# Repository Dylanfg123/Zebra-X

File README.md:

# ZeBra-X: A Xilinx Zynq Demo Board

The ZeBra-X board is my take on the Phil's Lab ZettBrett board. The heart of this board is a Xilinx Zynq (XC7Z010-2CLG400) SOC demo board featuring a 1Gig ethernet interface, USB-UART/USB-JTAG FTDI, USB HS, 1GB DDR3 memory, 4GB eMMC memory, and 16MB QSPI Flash. The main purpose of this board is to learn more about advanced PCB design techniques and get more familiar with the Xilinx software suite.

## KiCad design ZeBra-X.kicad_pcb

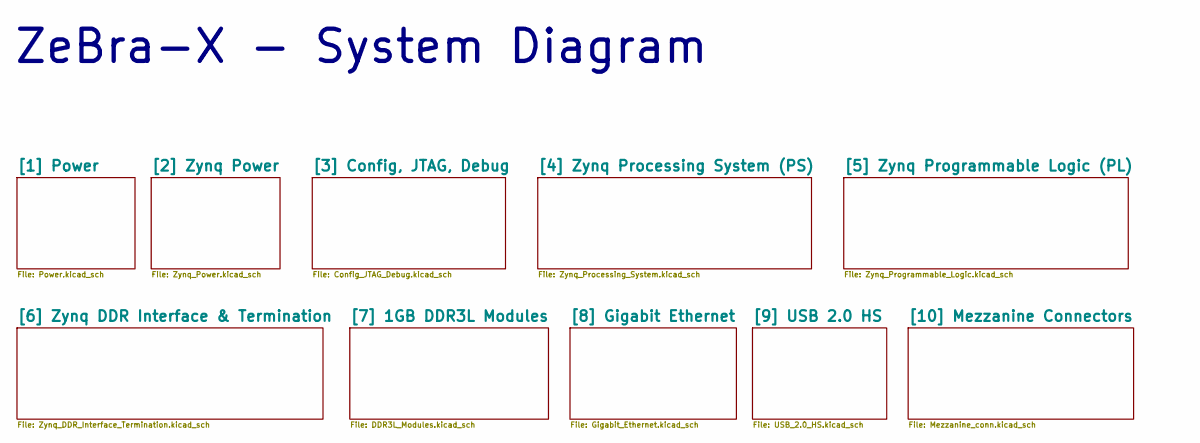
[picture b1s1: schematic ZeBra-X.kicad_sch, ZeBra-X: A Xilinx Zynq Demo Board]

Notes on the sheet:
ZeBra-X - System Diagram

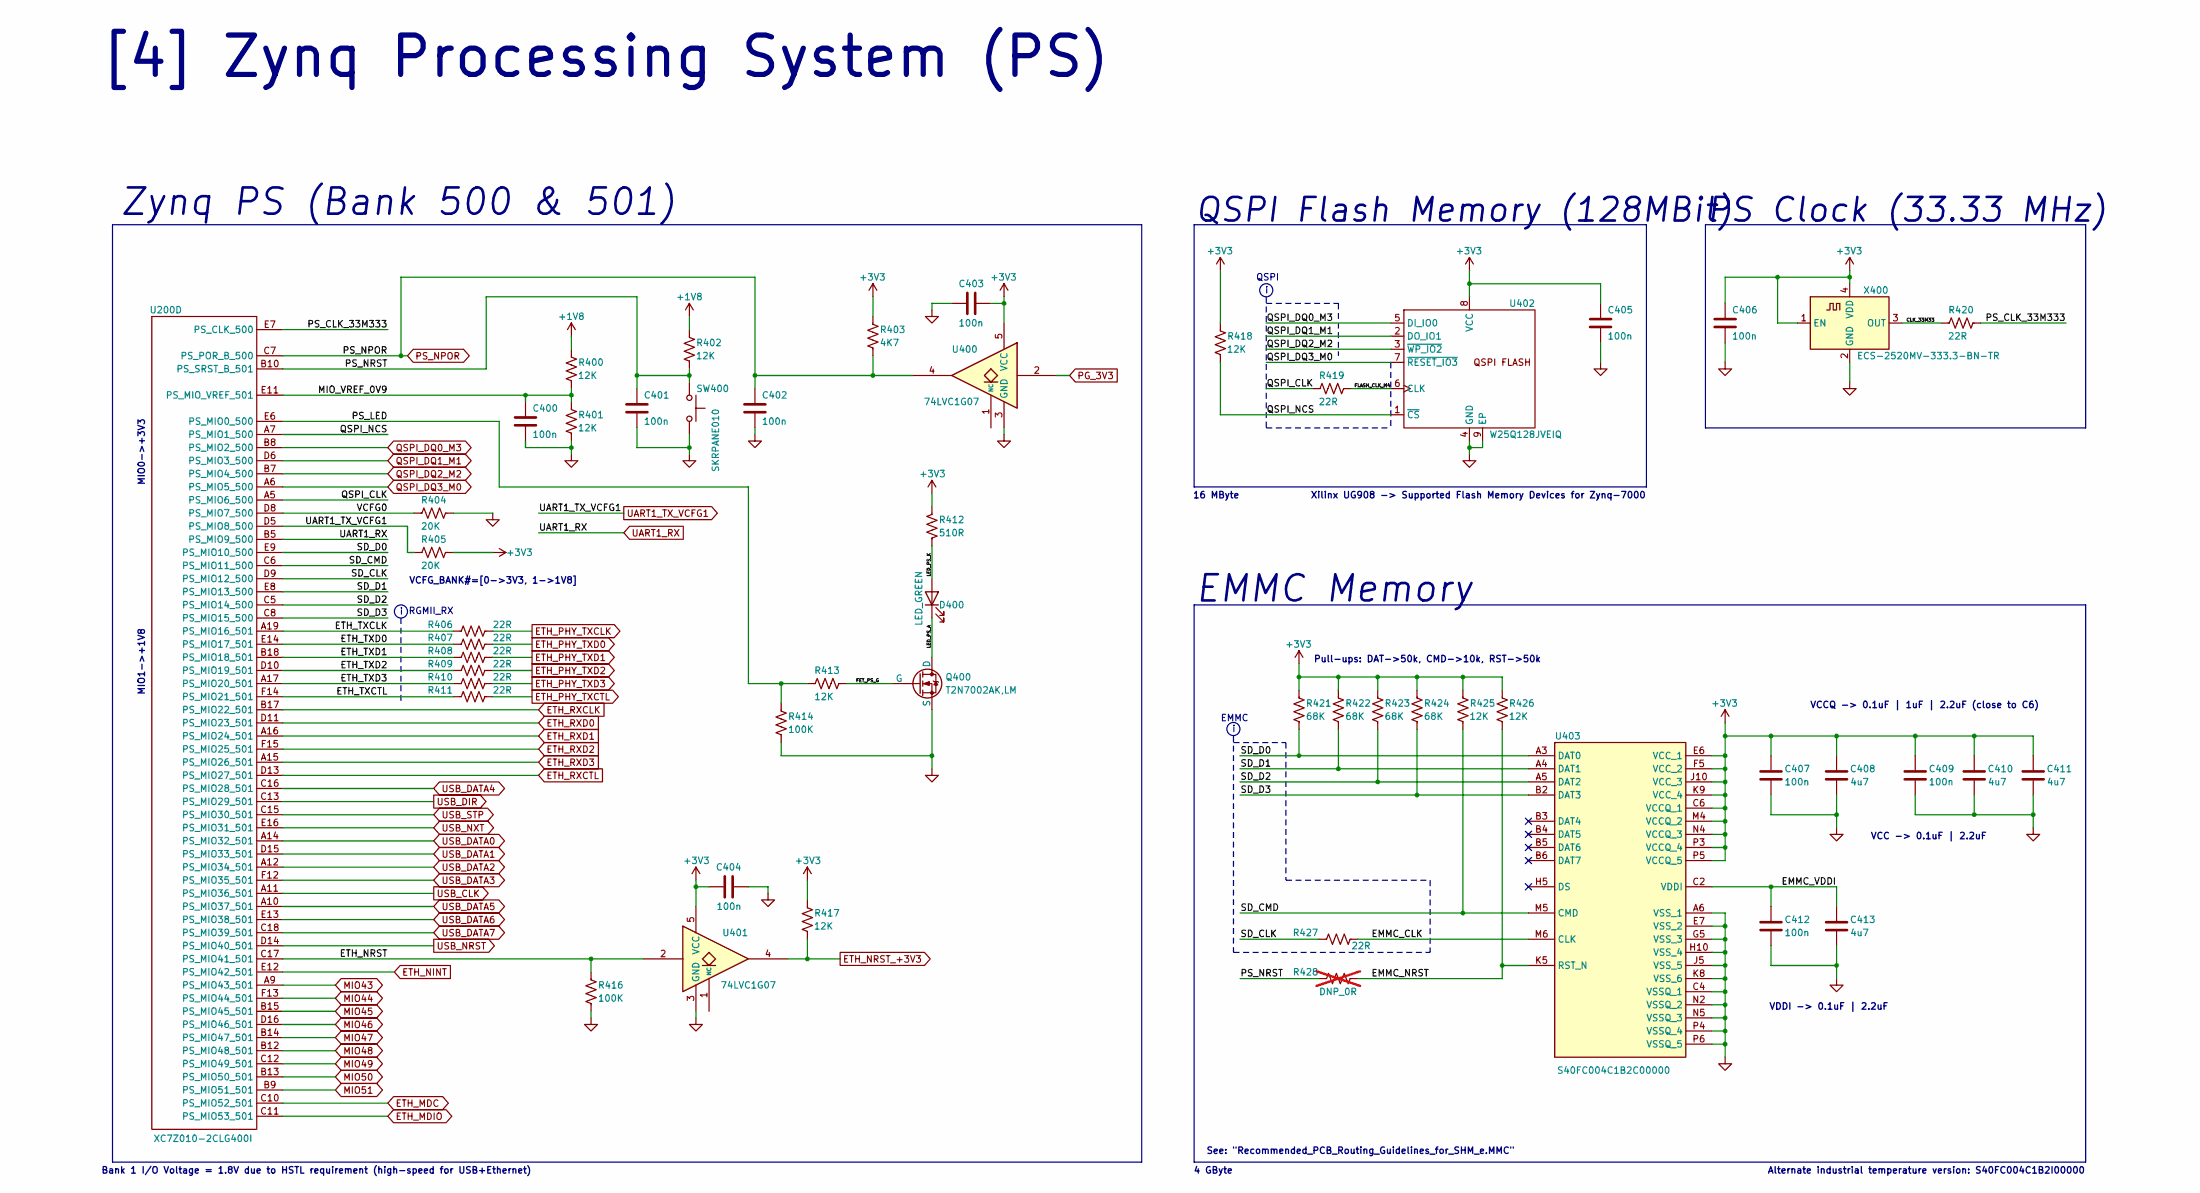
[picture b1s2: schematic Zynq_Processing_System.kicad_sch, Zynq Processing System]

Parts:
C400, C401, C402, C403, C404, C405, C406, C407, C409, C412: 100n; C_0402_1005Metric; Manufacturer PN CC0402KRX5R8BB104; LCSC PN C106256
C408, C410, C411, C413: 4u7; C_0402_1005Metric; Manufacturer PN CL05A475MP5NRNC; LCSC PN C23733
D400: LED_GREEN; LED_0402_1005Metric; Manufacturer PN SZYY0402YG; LCSC PN C434449
Q400: T2N7002AK,LM; SOT23_TOS; Manufacturer PN T2N7002AK,LM; LCSC PN C516175
R400, R401, R402, R413, R417, R418, R425, R426: 12K; R_0402_1005Metric; Manufacturer PN RTT021202FTH; LCSC PN C102781
R403: 4K7; R_0402_1005Metric; Manufacturer PN RC0402FR-074K7L; LCSC PN C105871
R404, R405: 20K; R_0402_1005Metric; Manufacturer PN RC0402FR-0720KL; LCSC PN C93942
R406, R407, R408, R409, R410, R411, R419, R420, R427: 22R; R_0402_1005Metric; Manufacturer PN RC0402FR-0722RL; LCSC PN C114765
R412: 510R; R_0402_1005Metric; Manufacturer PN RC0402FR-07510RL; LCSC PN C276273
R414, R416: 100K; R_0402_1005Metric; Manufacturer PN RC0402FR-07100KL; LCSC PN C60491
R421, R422, R423, R424: 68K; R_0402_1005Metric; Manufacturer PN RC0402FR-0768KL; LCSC PN C137947
R428: DNP_0R; R_0402_1005Metric; not fitted
SW400: SKRPANE010; SW_Push_1P1T_NO_Vertical_Wuerth_434133025816; Manufacturer PN SKRPANE010; LCSC PN C470426
U200: XC7Z010-2CLG400I; CLG400_XIL; Manufacturer PN XC7Z010-2CLG400I; LCSC PN C2840993
U400, U401: 74LVC1G07; SOT-23-5; Manufacturer PN SN74LVC1G07DBVT; LCSC PN C2867373
U402: W25Q128JVEIQ; WSON-8-1EP_8x6mm_P1.27mm_EP3.4x4.3mm; Manufacturer PN W25Q128JVEIQ
U403: S40FC004C1B2C00000; BGA153C50P14X14_900X750X80; Manufacturer PN S40FC004C1B2C00000
X400: ECS-2520MV-333.3-BN-TR; Oscillator_SMD_ECS_2520MV-xxx-xx-4Pin_2.5x2.0mm; Manufacturer PN ECS-2520MV-333.3-BN-TR

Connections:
+1V8: R400.2, R402.2; also elsewhere on the board
+3V3: C403.1, C404.1, C405.1, C406.1, C407.1, C408.2, C409.1, C410.2, C411.2, R403.1, R405.1, R412.2, R417.2, R418.2, R421.1, R422.1, R423.1, R424.1, R425.2, R426.2, U400.5 (VCC), U401.5 (VCC), U402.8 (VCC), U403.C6 (VCCQ_1), U403.E6 (VCC_1), U403.F5 (VCC_2), U403.J10 (VCC_3), U403.K9 (VCC_4), U403.M4 (VCCQ_2), U403.N4 (VCCQ_3), U403.P3 (VCCQ_4), U403.P5 (VCCQ_5), X400.1 (EN), X400.4 (VDD); also elsewhere on the board
/[4] Zynq Processing System (PS)/CLK_33M33: R420.1, X400.3 (OUT)
/[4] Zynq Processing System (PS)/EMMC_CLK: R427.2, U403.M6 (CLK)
/[4] Zynq Processing System (PS)/EMMC_NRST: R426.1, R428.1, U403.K5 (RST_N)
/[4] Zynq Processing System (PS)/EMMC_VDDI: C412.1, C413.2, U403.C2 (VDDI)
/[4] Zynq Processing System (PS)/ETH_NRST: R416.1, U200.C17 (PS_MIO41_501), U401.2
/[4] Zynq Processing System (PS)/ETH_TXCLK: R406.1, U200.A19 (PS_MIO16_501)
/[4] Zynq Processing System (PS)/ETH_TXCTL: R411.1, U200.F14 (PS_MIO21_501)
/[4] Zynq Processing System (PS)/ETH_TXD0: R407.1, U200.E14 (PS_MIO17_501)
/[4] Zynq Processing System (PS)/ETH_TXD1: R408.1, U200.B18 (PS_MIO18_501)
/[4] Zynq Processing System (PS)/ETH_TXD2: R409.1, U200.D10 (PS_MIO19_501)
/[4] Zynq Processing System (PS)/ETH_TXD3: R410.1, U200.A17 (PS_MIO20_501)
/[4] Zynq Processing System (PS)/FET_PS_G: Q400.1 (G), R413.1
/[4] Zynq Processing System (PS)/FLASH_CLK_M4: R419.2, U402.6 (CLK)
/[4] Zynq Processing System (PS)/LED_PS_A: D400.1 (K), Q400.3 (D)
/[4] Zynq Processing System (PS)/LED_PS_K: D400.2 (A), R412.1
/[4] Zynq Processing System (PS)/MIO_VREF_0V9: C400.1, R400.1, R401.2, U200.E11 (PS_MIO_VREF_501)
/[4] Zynq Processing System (PS)/PS_CLK_33M333: R420.2, U200.E7 (PS_CLK_500)
/[4] Zynq Processing System (PS)/PS_LED: R413.2, R414.1, U200.E6 (PS_MIO0_500)
/[4] Zynq Processing System (PS)/PS_NRST: C401.1, R402.1, R428.2, SW400.1, U200.B10 (PS_SRST_B_501)
/[4] Zynq Processing System (PS)/QSPI_CLK: R419.1, U200.A5 (PS_MIO6_500)
/[4] Zynq Processing System (PS)/QSPI_NCS: R418.1, U200.A7 (PS_MIO1_500), U402.1 (~CS)
/[4] Zynq Processing System (PS)/SD_CLK: R427.1, U200.D9 (PS_MIO12_500)
/[4] Zynq Processing System (PS)/SD_CMD: R425.1, U200.C6 (PS_MIO11_500), U403.M5 (CMD)
/[4] Zynq Processing System (PS)/SD_D0: R421.2, U200.E9 (PS_MIO10_500), U403.A3 (DAT0)
/[4] Zynq Processing System (PS)/SD_D1: R422.2, U200.E8 (PS_MIO13_500), U403.A4 (DAT1)
/[4] Zynq Processing System (PS)/SD_D2: R423.2, U200.C5 (PS_MIO14_500), U403.A5 (DAT2)
/[4] Zynq Processing System (PS)/SD_D3: R424.2, U200.C8 (PS_MIO15_500), U403.B2 (DAT3)
/[4] Zynq Processing System (PS)/VCFG0: R404.2, U200.D8 (PS_MIO7_500)
ETH_MDC: U200.C10 (PS_MIO52_501); also elsewhere on the board
ETH_MDIO: U200.C11 (PS_MIO53_501); also elsewhere on the board
ETH_NINT: U200.E12 (PS_MIO42_501); also elsewhere on the board
ETH_NRST_+3V3: R417.1, U401.4; also elsewhere on the board
ETH_PHY_TXCLK: R406.2; also elsewhere on the board
ETH_PHY_TXCTL: R411.2; also elsewhere on the board
ETH_PHY_TXD0: R407.2; also elsewhere on the board
ETH_PHY_TXD1: R408.2; also elsewhere on the board
ETH_PHY_TXD2: R409.2; also elsewhere on the board
ETH_PHY_TXD3: R410.2; also elsewhere on the board
ETH_RXCLK: U200.B17 (PS_MIO22_501); also elsewhere on the board
ETH_RXCTL: U200.D13 (PS_MIO27_501); also elsewhere on the board
ETH_RXD0: U200.D11 (PS_MIO23_501); also elsewhere on the board
ETH_RXD1: U200.A16 (PS_MIO24_501); also elsewhere on the board
ETH_RXD2: U200.F15 (PS_MIO25_501); also elsewhere on the board
ETH_RXD3: U200.A15 (PS_MIO26_501); also elsewhere on the board
GND: C400.2, C401.2, C402.2, C403.2, C404.2, C405.2, C406.2, C407.2, C408.1, C409.2, C410.1, C411.1, C412.2, C413.1, Q400.2 (S), R401.1, R404.1, R414.2, R416.2, SW400.2, U400.3 (GND), U401.3 (GND), U402.4 (GND), U402.9 (EP), U403.A6 (VSS_1), U403.C4 (VSSQ_1), U403.E7 (VSS_2), U403.G5 (VSS_3), U403.H10 (VSS_4), U403.J5 (VSS_5), U403.K8 (VSS_6), U403.N2 (VSSQ_2), U403.N5 (VSSQ_3), U403.P4 (VSSQ_4), U403.P6 (VSSQ_5), X400.2 (GND); also elsewhere on the board
MIO43: U200.A9 (PS_MIO43_501)
MIO44: U200.F13 (PS_MIO44_501)
MIO45: U200.B15 (PS_MIO45_501)
MIO46: U200.D16 (PS_MIO46_501)
MIO47: U200.B14 (PS_MIO47_501)
MIO48: U200.B12 (PS_MIO48_501)
MIO49: U200.C12 (PS_MIO49_501); also elsewhere on the board
MIO50: U200.B13 (PS_MIO50_501); also elsewhere on the board
MIO51: U200.B9 (PS_MIO51_501); also elsewhere on the board
PG_3V3: U400.2; also elsewhere on the board
PS_NPOR: C402.1, R403.2, U200.C7 (PS_POR_B_500), U400.4; also elsewhere on the board
QSPI_DQ0_M3: U200.B8 (PS_MIO2_500), U402.5 (DI_IO0); also elsewhere on the board
QSPI_DQ1_M1: U200.D6 (PS_MIO3_500), U402.2 (DO_IO1); also elsewhere on the board
QSPI_DQ2_M2: U200.B7 (PS_MIO4_500), U402.3 (~WP_IO2); also elsewhere on the board
QSPI_DQ3_M0: U200.A6 (PS_MIO5_500), U402.7 (~RESET_IO3); also elsewhere on the board
UART1_RX: U200.B5 (PS_MIO9_500); also elsewhere on the board
UART1_TX_VCFG1: R405.2, U200.D5 (PS_MIO8_500); also elsewhere on the board
USB_CLK: U200.A11 (PS_MIO36_501); also elsewhere on the board
USB_DATA0: U200.A14 (PS_MIO32_501); also elsewhere on the board
USB_DATA1: U200.D15 (PS_MIO33_501); also elsewhere on the board
USB_DATA2: U200.A12 (PS_MIO34_501); also elsewhere on the board
USB_DATA3: U200.F12 (PS_MIO35_501); also elsewhere on the board
USB_DATA4: U200.C16 (PS_MIO28_501); also elsewhere on the board
USB_DATA5: U200.A10 (PS_MIO37_501); also elsewhere on the board
USB_DATA6: U200.E13 (PS_MIO38_501); also elsewhere on the board
USB_DATA7: U200.C18 (PS_MIO39_501); also elsewhere on the board
USB_DIR: U200.C13 (PS_MIO29_501); also elsewhere on the board
USB_NRST: U200.D14 (PS_MIO40_501); also elsewhere on the board
USB_NXT: U200.E16 (PS_MIO31_501); also elsewhere on the board
USB_STP: U200.C15 (PS_MIO30_501); also elsewhere on the board

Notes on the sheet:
VCFG_BANK#=[0->3V3, 1->1V8]
16 MByte
See: "Recommended_PCB_Routing_Guidelines_for_SHM_e.MMC"
EMMC Memory
MIO1->+1V8
Xilinx UG908 -> Supported Flash Memory Devices for Zynq-7000
VDDI -> 0.1uF | 2.2uF
VCC -> 0.1uF | 2.2uF
Zynq PS (Bank 500 & 501)
RGMII_RX
QSPI
Alternate industrial temperature version: S40FC004C1B2I00000
Pull-ups: DAT->50k, CMD->10k, RST->50k
VCCQ -> 0.1uF | 1uF | 2.2uF (close to C6)
Bank 1 I/O Voltage = 1.8V due to HSTL requirement (high-speed for USB+Ethernet)
EMMC
4 GByte
QSPI Flash Memory (128MBit)
[4] Zynq Processing System (PS)
PS Clock (33.33 MHz)
MIO0->+3V3

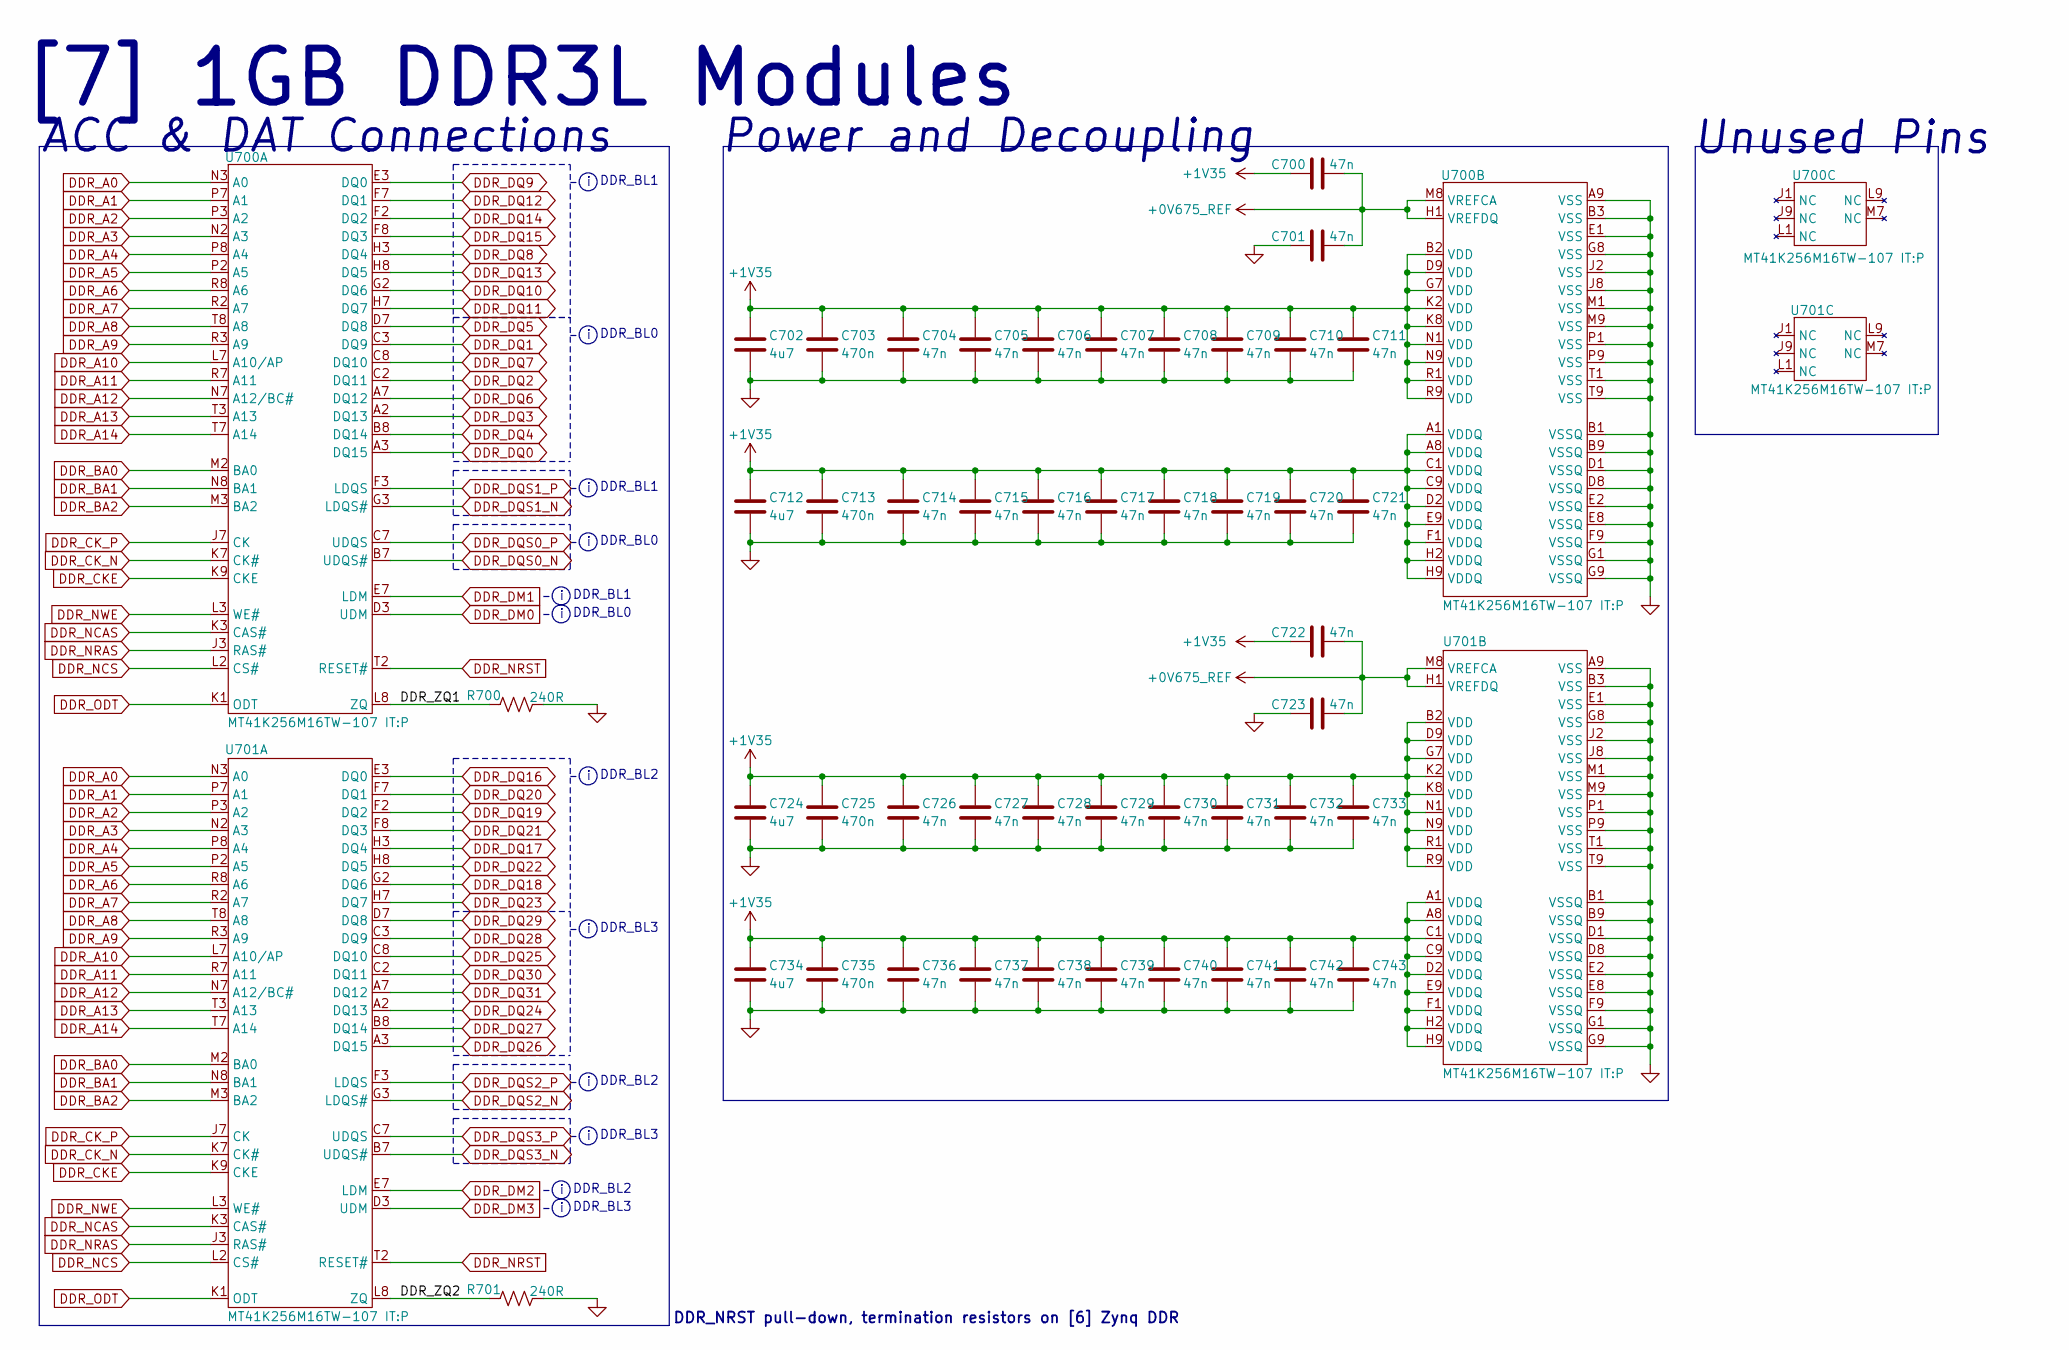
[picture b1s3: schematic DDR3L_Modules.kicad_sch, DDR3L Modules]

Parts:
C700, C701, C704, C705, C706, C707, C708, C709, C710, C711, C714, C715, C716, C717, C718, C719, C720, C721, C722, C723, C726, C727, C728, C729, C730, C731, C732, C733, C736, C737, C738, C739, C740, C741, C742, C743: 47n; C_0201_0603Metric; Manufacturer PN GRT033R60J473KE01D; LCSC PN C126621
C702, C712, C724, C734: 4u7; C_0402_1005Metric; Manufacturer PN CL05A475MP5NRNC; LCSC PN C23733
C703, C713, C725, C735: 470n; C_0201_0603Metric; Manufacturer PN GRM033R60J474KE90D; LCSC PN C85926
R700, R701: 240R; R_0402_1005Metric; Manufacturer PN RC0402FR-07240RL; LCSC PN C114755
U700, U701: MT41K256M16TW-107 IT:P; FBGA96_TW_MRN; Manufacturer PN MT41K256M16TW-107 IT:P; LCSC PN C367428

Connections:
+0V675_REF: C700.2, C701.2, C722.2, C723.2, U700.H1 (VREFDQ), U700.M8 (VREFCA), U701.H1 (VREFDQ), U701.M8 (VREFCA); also elsewhere on the board
+1V35: C700.1, C702.1, C703.1, C704.1, C705.1, C706.1, C707.1, C708.1, C709.1, C710.1, C711.1, C712.1, C713.1, C714.1, C715.1, C716.1, C717.1, C718.1, C719.1, C720.1, C721.1, C722.1, C724.1, C725.1, C726.1, C727.1, C728.1, C729.1, C730.1, C731.1, C732.1, C733.1, C734.1, C735.1, C736.1, C737.1, C738.1, C739.1, C740.1, C741.1, C742.1, C743.1, U700.A1 (VDDQ), U700.A8 (VDDQ), U700.B2 (VDD), U700.C1 (VDDQ), U700.C9 (VDDQ), U700.D2 (VDDQ), U700.D9 (VDD), U700.E9 (VDDQ), U700.F1 (VDDQ), U700.G7 (VDD), U700.H2 (VDDQ), U700.H9 (VDDQ), U700.K2 (VDD), U700.K8 (VDD), U700.N1 (VDD), U700.N9 (VDD), U700.R1 (VDD), U700.R9 (VDD), U701.A1 (VDDQ), U701.A8 (VDDQ), U701.B2 (VDD), U701.C1 (VDDQ), U701.C9 (VDDQ), U701.D2 (VDDQ), U701.D9 (VDD), U701.E9 (VDDQ), U701.F1 (VDDQ), U701.G7 (VDD), U701.H2 (VDDQ), U701.H9 (VDDQ), U701.K2 (VDD), U701.K8 (VDD), U701.N1 (VDD), U701.N9 (VDD), U701.R1 (VDD), U701.R9 (VDD); also elsewhere on the board
/[7] 1GB DDR3L Modules/DDR_ZQ1: R700.1, U700.L8 (ZQ)
/[7] 1GB DDR3L Modules/DDR_ZQ2: R701.1, U701.L8 (ZQ)
DDR_A0: U700.N3 (A0), U701.N3 (A0); also elsewhere on the board
DDR_A1: U700.P7 (A1), U701.P7 (A1); also elsewhere on the board
DDR_A2: U700.P3 (A2), U701.P3 (A2); also elsewhere on the board
DDR_A3: U700.N2 (A3), U701.N2 (A3); also elsewhere on the board
DDR_A4: U700.P8 (A4), U701.P8 (A4); also elsewhere on the board
DDR_A5: U700.P2 (A5), U701.P2 (A5); also elsewhere on the board
DDR_A6: U700.R8 (A6), U701.R8 (A6); also elsewhere on the board
DDR_A7: U700.R2 (A7), U701.R2 (A7); also elsewhere on the board
DDR_A8: U700.T8 (A8), U701.T8 (A8); also elsewhere on the board
DDR_A9: U700.R3 (A9), U701.R3 (A9); also elsewhere on the board
DDR_A10: U700.L7 (A10/AP), U701.L7 (A10/AP); also elsewhere on the board
DDR_A11: U700.R7 (A11), U701.R7 (A11); also elsewhere on the board
DDR_A12: U700.N7 (A12/BC#), U701.N7 (A12/BC#); also elsewhere on the board
DDR_A13: U700.T3 (A13), U701.T3 (A13); also elsewhere on the board
DDR_A14: U700.T7 (A14), U701.T7 (A14); also elsewhere on the board
DDR_BA0: U700.M2 (BA0), U701.M2 (BA0); also elsewhere on the board
DDR_BA1: U700.N8 (BA1), U701.N8 (BA1); also elsewhere on the board
DDR_BA2: U700.M3 (BA2), U701.M3 (BA2); also elsewhere on the board
DDR_CKE: U700.K9 (CKE), U701.K9 (CKE); also elsewhere on the board
DDR_CK_N: U700.K7 (CK#), U701.K7 (CK#); also elsewhere on the board
DDR_CK_P: U700.J7 (CK), U701.J7 (CK); also elsewhere on the board
DDR_DM0: U700.D3 (UDM); also elsewhere on the board
DDR_DM1: U700.E7 (LDM); also elsewhere on the board
DDR_DM2: U701.E7 (LDM); also elsewhere on the board
DDR_DM3: U701.D3 (UDM); also elsewhere on the board
DDR_DQ0: U700.A3 (DQ15); also elsewhere on the board
DDR_DQ1: U700.C3 (DQ9); also elsewhere on the board
DDR_DQ2: U700.C2 (DQ11); also elsewhere on the board
DDR_DQ3: U700.A2 (DQ13); also elsewhere on the board
DDR_DQ4: U700.B8 (DQ14); also elsewhere on the board
DDR_DQ5: U700.D7 (DQ8); also elsewhere on the board
DDR_DQ6: U700.A7 (DQ12); also elsewhere on the board
DDR_DQ7: U700.C8 (DQ10); also elsewhere on the board
DDR_DQ8: U700.H3 (DQ4); also elsewhere on the board
DDR_DQ9: U700.E3 (DQ0); also elsewhere on the board
DDR_DQ10: U700.G2 (DQ6); also elsewhere on the board
DDR_DQ11: U700.H7 (DQ7); also elsewhere on the board
DDR_DQ12: U700.F7 (DQ1); also elsewhere on the board
DDR_DQ13: U700.H8 (DQ5); also elsewhere on the board
DDR_DQ14: U700.F2 (DQ2); also elsewhere on the board
DDR_DQ15: U700.F8 (DQ3); also elsewhere on the board
DDR_DQ16: U701.E3 (DQ0); also elsewhere on the board
DDR_DQ17: U701.H3 (DQ4); also elsewhere on the board
DDR_DQ18: U701.G2 (DQ6); also elsewhere on the board
DDR_DQ19: U701.F2 (DQ2); also elsewhere on the board
DDR_DQ20: U701.F7 (DQ1); also elsewhere on the board
DDR_DQ21: U701.F8 (DQ3); also elsewhere on the board
DDR_DQ22: U701.H8 (DQ5); also elsewhere on the board
DDR_DQ23: U701.H7 (DQ7); also elsewhere on the board
DDR_DQ24: U701.A2 (DQ13); also elsewhere on the board
DDR_DQ25: U701.C8 (DQ10); also elsewhere on the board
DDR_DQ26: U701.A3 (DQ15); also elsewhere on the board
DDR_DQ27: U701.B8 (DQ14); also elsewhere on the board
DDR_DQ28: U701.C3 (DQ9); also elsewhere on the board
DDR_DQ29: U701.D7 (DQ8); also elsewhere on the board
DDR_DQ30: U701.C2 (DQ11); also elsewhere on the board
DDR_DQ31: U701.A7 (DQ12); also elsewhere on the board
DDR_DQS0_N: U700.B7 (UDQS#); also elsewhere on the board
DDR_DQS0_P: U700.C7 (UDQS); also elsewhere on the board
DDR_DQS1_N: U700.G3 (LDQS#); also elsewhere on the board
DDR_DQS1_P: U700.F3 (LDQS); also elsewhere on the board
DDR_DQS2_N: U701.G3 (LDQS#); also elsewhere on the board
DDR_DQS2_P: U701.F3 (LDQS); also elsewhere on the board
DDR_DQS3_N: U701.B7 (UDQS#); also elsewhere on the board
DDR_DQS3_P: U701.C7 (UDQS); also elsewhere on the board
DDR_NCAS: U700.K3 (CAS#), U701.K3 (CAS#); also elsewhere on the board
DDR_NCS: U700.L2 (CS#), U701.L2 (CS#); also elsewhere on the board
DDR_NRAS: U700.J3 (RAS#), U701.J3 (RAS#); also elsewhere on the board
DDR_NRST: U700.T2 (RESET#), U701.T2 (RESET#); also elsewhere on the board
DDR_NWE: U700.L3 (WE#), U701.L3 (WE#); also elsewhere on the board
DDR_ODT: U700.K1 (ODT), U701.K1 (ODT); also elsewhere on the board
GND: C701.1, C702.2, C703.2, C704.2, C705.2, C706.2, C707.2, C708.2, C709.2, C710.2, C711.2, C712.2, C713.2, C714.2, C715.2, C716.2, C717.2, C718.2, C719.2, C720.2, C721.2, C723.1, C724.2, C725.2, C726.2, C727.2, C728.2, C729.2, C730.2, C731.2, C732.2, C733.2, C734.2, C735.2, C736.2, C737.2, C738.2, C739.2, C740.2, C741.2, C742.2, C743.2, R700.2, R701.2, U700.A9 (VSS), U700.B1 (VSSQ), U700.B3 (VSS), U700.B9 (VSSQ), U700.D1 (VSSQ), U700.D8 (VSSQ), U700.E1 (VSS), U700.E2 (VSSQ), U700.E8 (VSSQ), U700.F9 (VSSQ), U700.G1 (VSSQ), U700.G8 (VSS), U700.G9 (VSSQ), U700.J2 (VSS), U700.J8 (VSS), U700.M1 (VSS), U700.M9 (VSS), U700.P1 (VSS), U700.P9 (VSS), U700.T1 (VSS), U700.T9 (VSS), U701.A9 (VSS), U701.B1 (VSSQ), U701.B3 (VSS), U701.B9 (VSSQ), U701.D1 (VSSQ), U701.D8 (VSSQ), U701.E1 (VSS), U701.E2 (VSSQ), U701.E8 (VSSQ), U701.F9 (VSSQ), U701.G1 (VSSQ), U701.G8 (VSS), U701.G9 (VSSQ), U701.J2 (VSS), U701.J8 (VSS), U701.M1 (VSS), U701.M9 (VSS), U701.P1 (VSS), U701.P9 (VSS), U701.T1 (VSS), U701.T9 (VSS); also elsewhere on the board

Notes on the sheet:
DDR_BL2
DDR_BL0
ACC & DAT Connections
DDR_BL3
DDR_BL1
Unused Pins
[7] 1GB DDR3L Modules
DDR_NRST pull-down, termination resistors on [6] Zynq DDR
Power and Decoupling
DDR_BL1

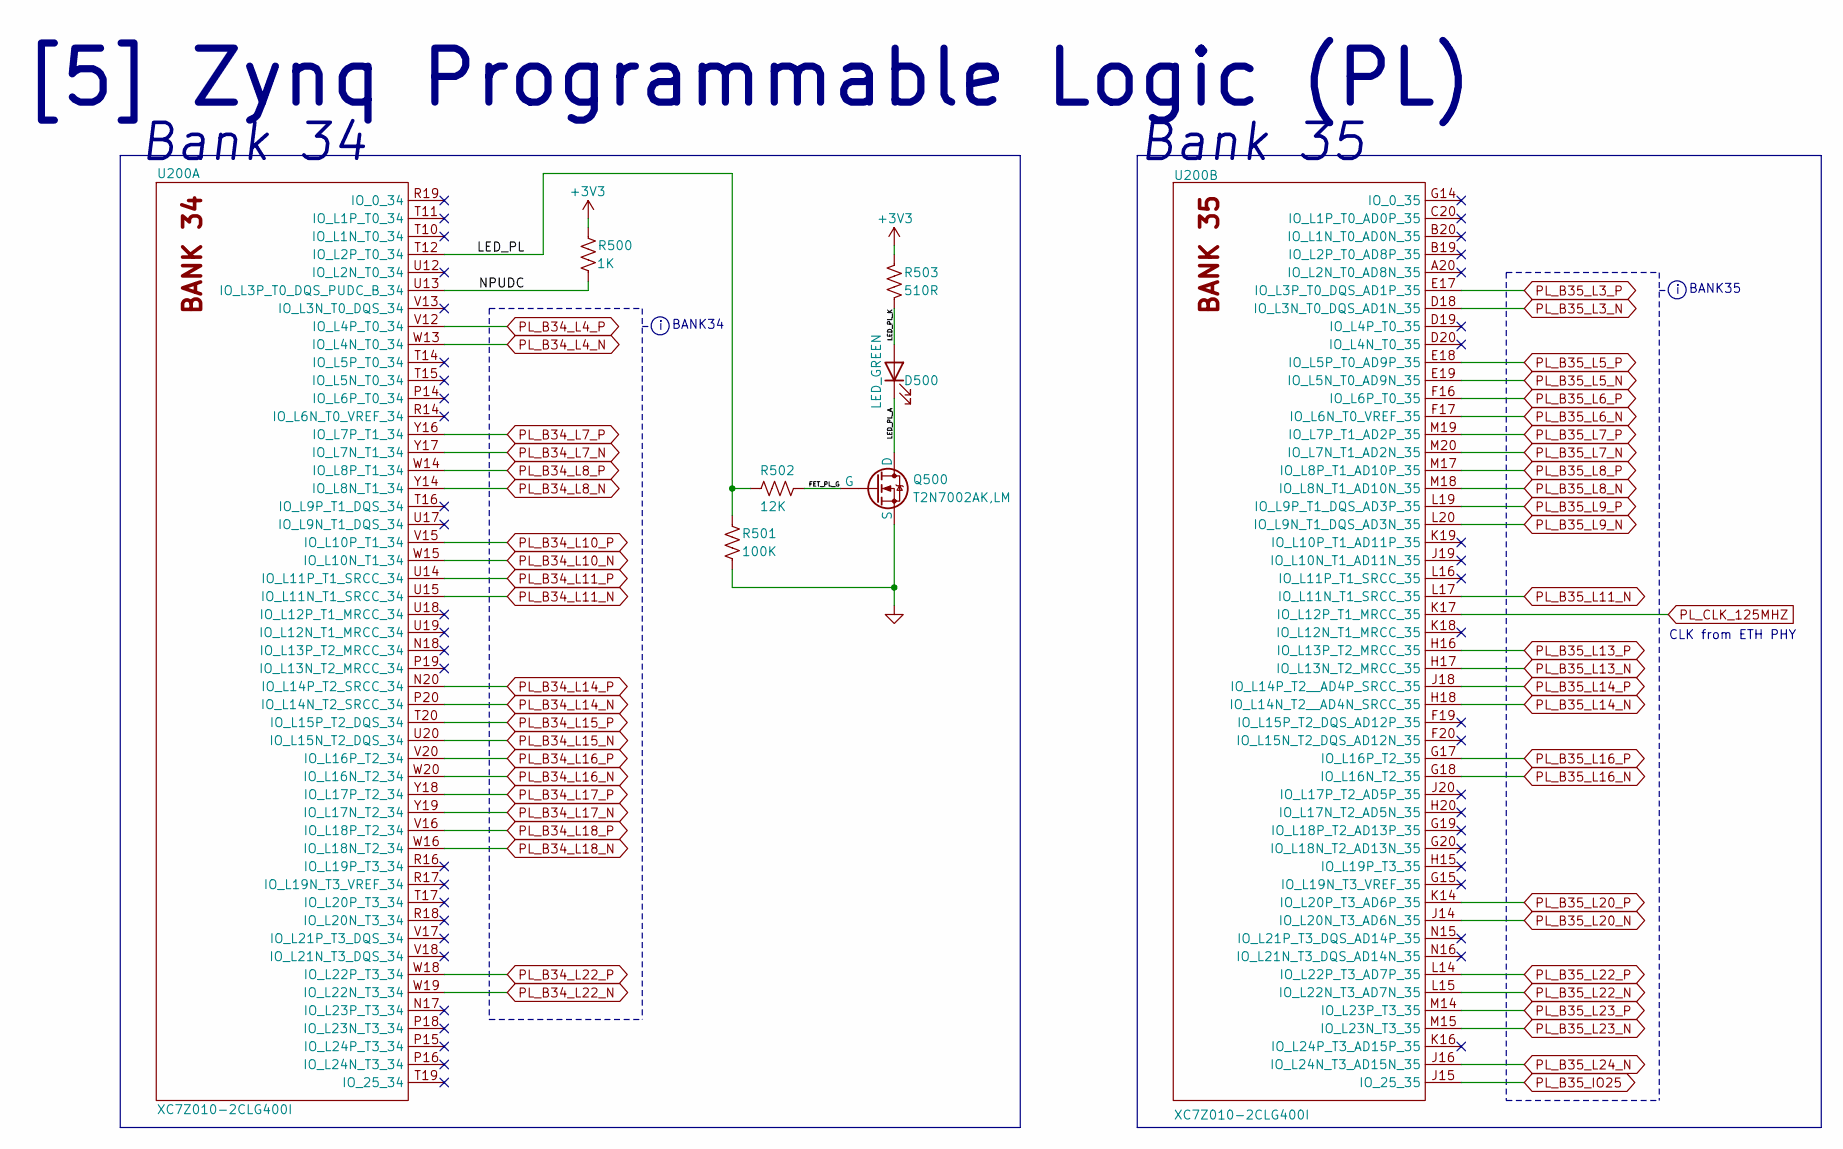
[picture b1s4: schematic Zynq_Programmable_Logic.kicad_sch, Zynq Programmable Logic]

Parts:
D500: LED_GREEN; LED_0402_1005Metric; Manufacturer PN SZYY0402YG; LCSC PN C434449
Q500: T2N7002AK,LM; SOT23_TOS; Manufacturer PN T2N7002AK,LM; LCSC PN C516175
R500: 1K; R_0402_1005Metric; Manufacturer PN RC0402FR-071KL; LCSC PN C106235
R501: 100K; R_0402_1005Metric; Manufacturer PN RC0402FR-07100KL; LCSC PN C60491
R502: 12K; R_0402_1005Metric; Manufacturer PN RTT021202FTH; LCSC PN C102781
R503: 510R; R_0402_1005Metric; Manufacturer PN RC0402FR-07510RL; LCSC PN C276273
U200: XC7Z010-2CLG400I; CLG400_XIL; Manufacturer PN XC7Z010-2CLG400I; LCSC PN C2840993

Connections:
+3V3: R500.2, R503.2; also elsewhere on the board
/[5] Zynq Programmable Logic (PL)/FET_PL_G: Q500.1 (G), R502.1
/[5] Zynq Programmable Logic (PL)/LED_PL: R501.1, R502.2, U200.T12 (IO_L2P_T0_34)
/[5] Zynq Programmable Logic (PL)/LED_PL_A: D500.1 (K), Q500.3 (D)
/[5] Zynq Programmable Logic (PL)/LED_PL_K: D500.2 (A), R503.1
/[5] Zynq Programmable Logic (PL)/NPUDC: R500.1, U200.U13 (IO_L3P_T0_DQS_PUDC_B_34)
GND: Q500.2 (S), R501.2; also elsewhere on the board
PL_B34_L4_N: U200.W13 (IO_L4N_T0_34); also elsewhere on the board
PL_B34_L4_P: U200.V12 (IO_L4P_T0_34); also elsewhere on the board
PL_B34_L7_N: U200.Y17 (IO_L7N_T1_34); also elsewhere on the board
PL_B34_L7_P: U200.Y16 (IO_L7P_T1_34); also elsewhere on the board
PL_B34_L8_N: U200.Y14 (IO_L8N_T1_34); also elsewhere on the board
PL_B34_L8_P: U200.W14 (IO_L8P_T1_34); also elsewhere on the board
PL_B34_L10_N: U200.W15 (IO_L10N_T1_34); also elsewhere on the board
PL_B34_L10_P: U200.V15 (IO_L10P_T1_34); also elsewhere on the board
PL_B34_L11_N: U200.U15 (IO_L11N_T1_SRCC_34); also elsewhere on the board
PL_B34_L11_P: U200.U14 (IO_L11P_T1_SRCC_34); also elsewhere on the board
PL_B34_L14_N: U200.P20 (IO_L14N_T2_SRCC_34); also elsewhere on the board
PL_B34_L14_P: U200.N20 (IO_L14P_T2_SRCC_34); also elsewhere on the board
PL_B34_L15_N: U200.U20 (IO_L15N_T2_DQS_34); also elsewhere on the board
PL_B34_L15_P: U200.T20 (IO_L15P_T2_DQS_34); also elsewhere on the board
PL_B34_L16_N: U200.W20 (IO_L16N_T2_34); also elsewhere on the board
PL_B34_L16_P: U200.V20 (IO_L16P_T2_34); also elsewhere on the board
PL_B34_L17_N: U200.Y19 (IO_L17N_T2_34); also elsewhere on the board
PL_B34_L17_P: U200.Y18 (IO_L17P_T2_34); also elsewhere on the board
PL_B34_L18_N: U200.W16 (IO_L18N_T2_34); also elsewhere on the board
PL_B34_L18_P: U200.V16 (IO_L18P_T2_34); also elsewhere on the board
PL_B34_L22_N: U200.W19 (IO_L22N_T3_34); also elsewhere on the board
PL_B34_L22_P: U200.W18 (IO_L22P_T3_34); also elsewhere on the board
PL_B35_IO25: U200.J15 (IO_25_35); also elsewhere on the board
PL_B35_L3_N: U200.D18 (IO_L3N_T0_DQS_AD1N_35); also elsewhere on the board
PL_B35_L3_P: U200.E17 (IO_L3P_T0_DQS_AD1P_35); also elsewhere on the board
PL_B35_L5_N: U200.E19 (IO_L5N_T0_AD9N_35); also elsewhere on the board
PL_B35_L5_P: U200.E18 (IO_L5P_T0_AD9P_35); also elsewhere on the board
PL_B35_L6_N: U200.F17 (IO_L6N_T0_VREF_35); also elsewhere on the board
PL_B35_L6_P: U200.F16 (IO_L6P_T0_35); also elsewhere on the board
PL_B35_L7_N: U200.M20 (IO_L7N_T1_AD2N_35); also elsewhere on the board
PL_B35_L7_P: U200.M19 (IO_L7P_T1_AD2P_35); also elsewhere on the board
PL_B35_L8_N: U200.M18 (IO_L8N_T1_AD10N_35); also elsewhere on the board
PL_B35_L8_P: U200.M17 (IO_L8P_T1_AD10P_35); also elsewhere on the board
PL_B35_L9_N: U200.L20 (IO_L9N_T1_DQS_AD3N_35); also elsewhere on the board
PL_B35_L9_P: U200.L19 (IO_L9P_T1_DQS_AD3P_35); also elsewhere on the board
PL_B35_L11_N: U200.L17 (IO_L11N_T1_SRCC_35); also elsewhere on the board
PL_B35_L13_N: U200.H17 (IO_L13N_T2_MRCC_35); also elsewhere on the board
PL_B35_L13_P: U200.H16 (IO_L13P_T2_MRCC_35); also elsewhere on the board
PL_B35_L14_N: U200.H18 (IO_L14N_T2__AD4N_SRCC_35); also elsewhere on the board
PL_B35_L14_P: U200.J18 (IO_L14P_T2__AD4P_SRCC_35); also elsewhere on the board
PL_B35_L16_N: U200.G18 (IO_L16N_T2_35); also elsewhere on the board
PL_B35_L16_P: U200.G17 (IO_L16P_T2_35); also elsewhere on the board
PL_B35_L20_N: U200.J14 (IO_L20N_T3_AD6N_35); also elsewhere on the board
PL_B35_L20_P: U200.K14 (IO_L20P_T3_AD6P_35); also elsewhere on the board
PL_B35_L22_N: U200.L15 (IO_L22N_T3_AD7N_35); also elsewhere on the board
PL_B35_L22_P: U200.L14 (IO_L22P_T3_AD7P_35); also elsewhere on the board
PL_B35_L23_N: U200.M15 (IO_L23N_T3_35); also elsewhere on the board
PL_B35_L23_P: U200.M14 (IO_L23P_T3_35); also elsewhere on the board
PL_B35_L24_N: U200.J16 (IO_L24N_T3_AD15N_35); also elsewhere on the board
PL_CLK_125MHZ: U200.K17 (IO_L12P_T1_MRCC_35); also elsewhere on the board

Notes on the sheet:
Bank 35
BANK35
BANK34
[5] Zynq Programmable Logic (PL)
CLK from ETH PHY
Bank 34
